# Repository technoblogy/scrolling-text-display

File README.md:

# Scrolling Text Display
A scrolling text display that you can edit using a keyboard, based on four 8x8 LED dot-matrix displays, and controlled by an ATtiny85.

For more information see <http://www.technoblogy.com/show?4WX8>.

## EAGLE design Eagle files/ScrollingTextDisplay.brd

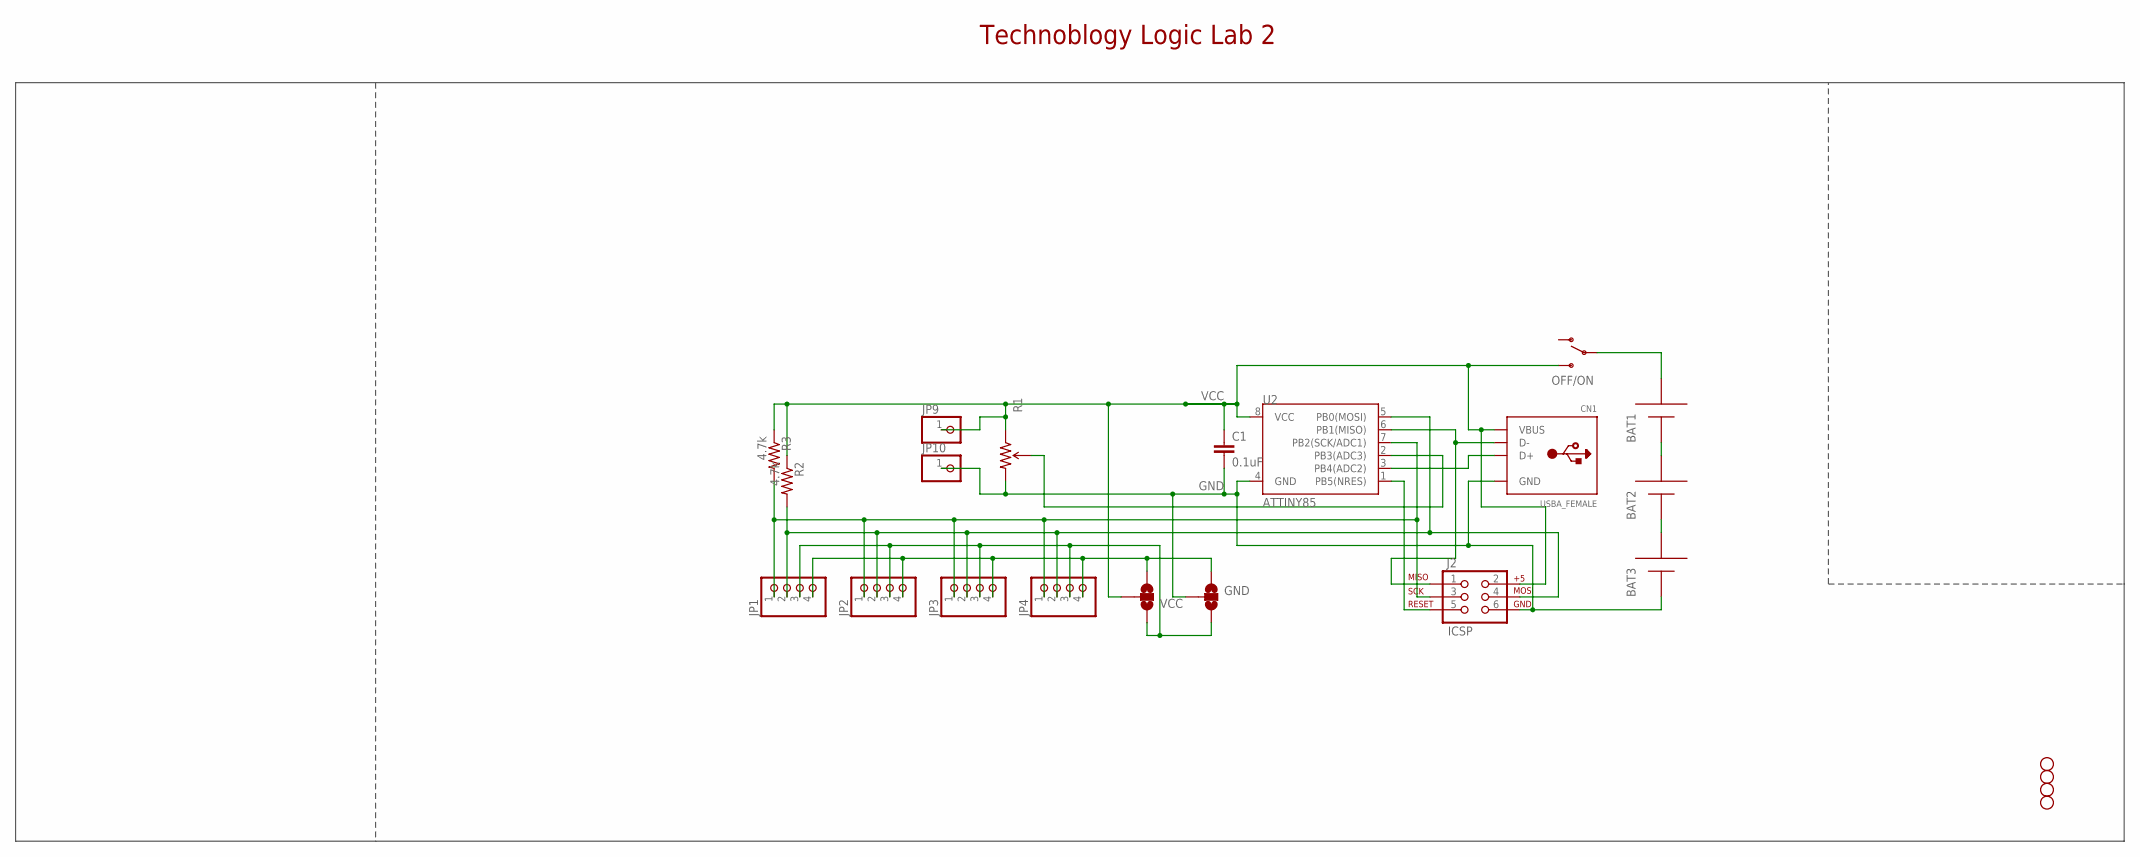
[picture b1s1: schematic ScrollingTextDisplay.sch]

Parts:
BAT1, BAT2, BAT3: AAA; 12BH412
C1: 0.1uF; CAP-PTH-SMALL-KIT
CN1: USBA_FEMALE; USB_HOST-PTH
GND: JUMPER-PAD-3-NOFULL_BOX_SILK; PAD-JUMPER-3-NO_YES_SILK_FULL_BOX
J2: ICSP; 2X3
JP1, JP2, JP3, JP4: HEADER-1X4ROUND; 1X04_ROUND
JP5, JP6, JP7, JP8: STAND-OFF
JP9, JP10: HEADER-1X1ROUND; 1X01_ROUND
OFF/ON: SWITCH-SPDTKIT; SWITCH-SPDT_KIT
R1: TRIMPOTPTH; TRIM_POT_PTH
R2, R3: 4.7k; AXIAL-0.3
U2: ATTINY85; DIP08
VCC: JUMPER-PAD-3-NOFULL_BOX_SILK; PAD-JUMPER-3-NO_YES_SILK_FULL_BOX

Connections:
END: GND.1, JP1.4, JP2.4, JP3.4, JP4.4, VCC.3
GND: BAT3.-, C1.2, CN1.GND, GND.2, J2.6, JP10.1, R1.3 (CW), U2.4 (GND)
MID: GND.3, JP1.3, JP2.3, JP3.3, JP4.3, VCC.1
unnamed: R1.2 (WIPER), U2.2 (PB3(ADC3))
unnamed: BAT1.+, OFF/ON.2
unnamed: BAT1.-, BAT2.+
unnamed: BAT2.-, BAT3.+
unnamed: J2.4, JP1.2, JP2.2, JP3.2, JP4.2, R2.P$2 (2), U2.5 (PB0(MOSI))
unnamed: J2.3, JP1.1, JP2.1, JP3.1, JP4.1, R3.P$2 (2), U2.7 (PB2(SCK/ADC1))
unnamed: CN1.D-, J2.1, U2.6 (PB1(MISO))
unnamed: CN1.D+, U2.3 (PB4(ADC2))
unnamed: J2.5, U2.1 (PB5(NRES))
VCC: C1.1, CN1.VBUS, J2.2, JP9.1, OFF/ON.3 (S), R1.1 (CCW), R2.P$1 (1), R3.P$1 (1), U2.8 (VCC), VCC.2

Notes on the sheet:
Technoblogy Logic Lab 2

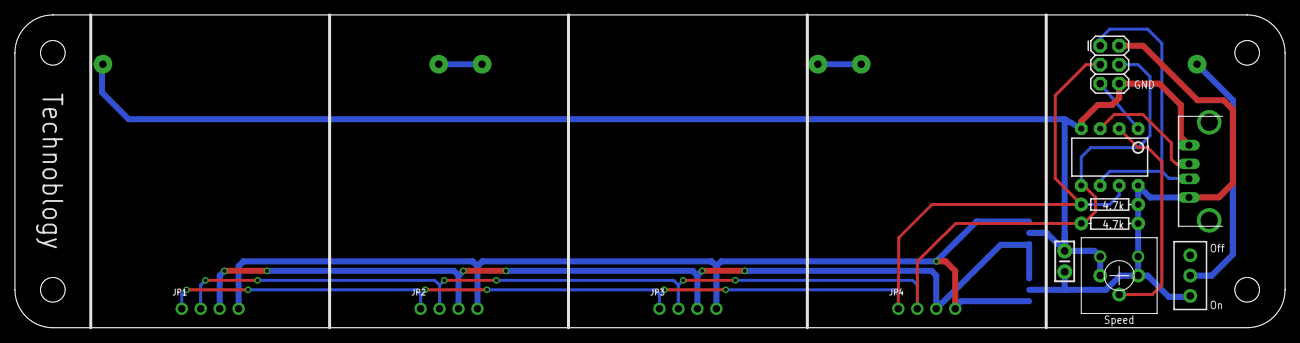
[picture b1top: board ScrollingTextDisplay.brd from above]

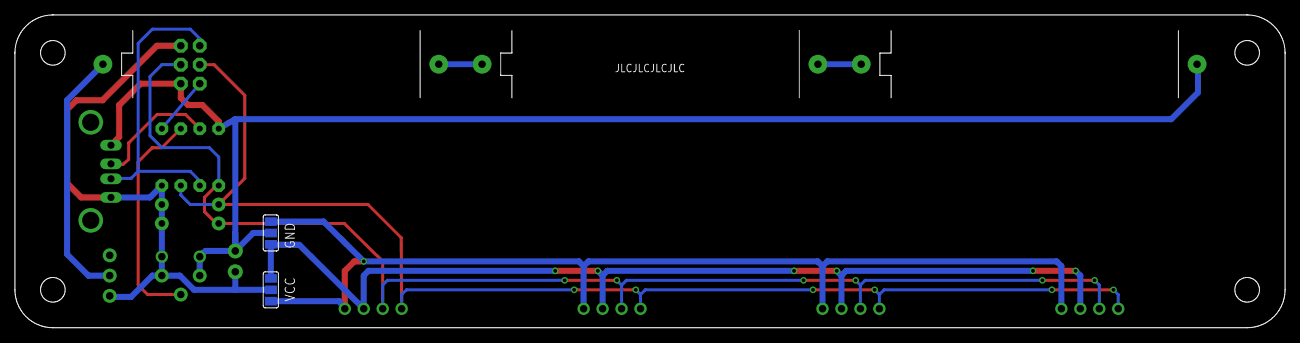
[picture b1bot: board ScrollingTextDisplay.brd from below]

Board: 2 copper layers, 170.2 x 41.9 mm, 23 parts (5 on the bottom side), 13 nets.

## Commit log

2024-12-16 Eagle and Gerber files

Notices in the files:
parts and their libraries:
SparkFun-Electromechanical: Licensing: Creative Commons ShareAlike 4.0 International - https://creativecommons.org/licenses/by-sa/4.0
microbuilder: This work is placed in the public domain, and may be freely used for commercial and non-commercial work with the following conditions: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
